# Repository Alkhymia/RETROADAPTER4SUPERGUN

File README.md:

# RETROADAPTER4SUPERGUN

Uses the concept of Paul Quereshi's RetroAdapter, but with CommonGround-Output instead of USB.
Lets you connect a wide range of controllers to a supergun or JAMMA incl SNES, MD, SAT, PSX, N64 etc.

## Work in progress

Right now, only the pcb is provided. The Code for the RetroAdapterMod needs to be rewritten because the pins changed!
If you would like to help finish this project, any help is appreciated.

## PCB Specification

You can order the printed circuit board e.g. from itead.cc using the GERBER files that I provided.

```
50 x 50 mm
1.2 to 1.6 (recommended) mm Thickness
HASL
```

### Installing

* solder all components to the pcb
* Atmega µController needs to be flashed via ISP-PORT.
* connect your favourite joypad to either the DB9 or DB15 connector as shown in the original connection diagram. Bare in mind that the pins may have changed! A detailed new connection diagram will follow in the future.
* connect the output to your JAMMA or SUPERGUN setup.
* Play your arcade games with your favourite controller, such as the Sega Saturn or SNES joypad.

## Links

* Original source for "USB Retropad Adapter" from Bruno Freitas acquired via http://www.brunofreitas.com/node/41 (included for reference in folder original_Files)

* Original source for "Retro Adapter v2.1a" from Paul Qureshi acquired via http://denki.world3.net/retro_v2.html (incuded for reference in folder original_Files)

* https://github.com/rsn8887/RetroAdapterMod

## Built With

* [EAGLE](https://www.autodesk.de/products/eagle/overview)

## Contributing

Please read [CONTRIBUTING.md] for details on our code of conduct, and the process for submitting pull requests to us.

## Authors

* **Alex Schütz** - *Concept & PCB Design*
* **rsn8887** - *RetroAdapterMod*
* **Paul Qureshi** - *RetroAdapter*

See also the list of [contributors](https://github.com/your/project/contributors) who participated in this project.

## License

This project is licensed under the MIT License - see the [LICENSE.md](LICENSE.md) file for details

## Acknowledgments

* This is a work in progress.
* Don't mess with electronics if you don't know what you're doing!

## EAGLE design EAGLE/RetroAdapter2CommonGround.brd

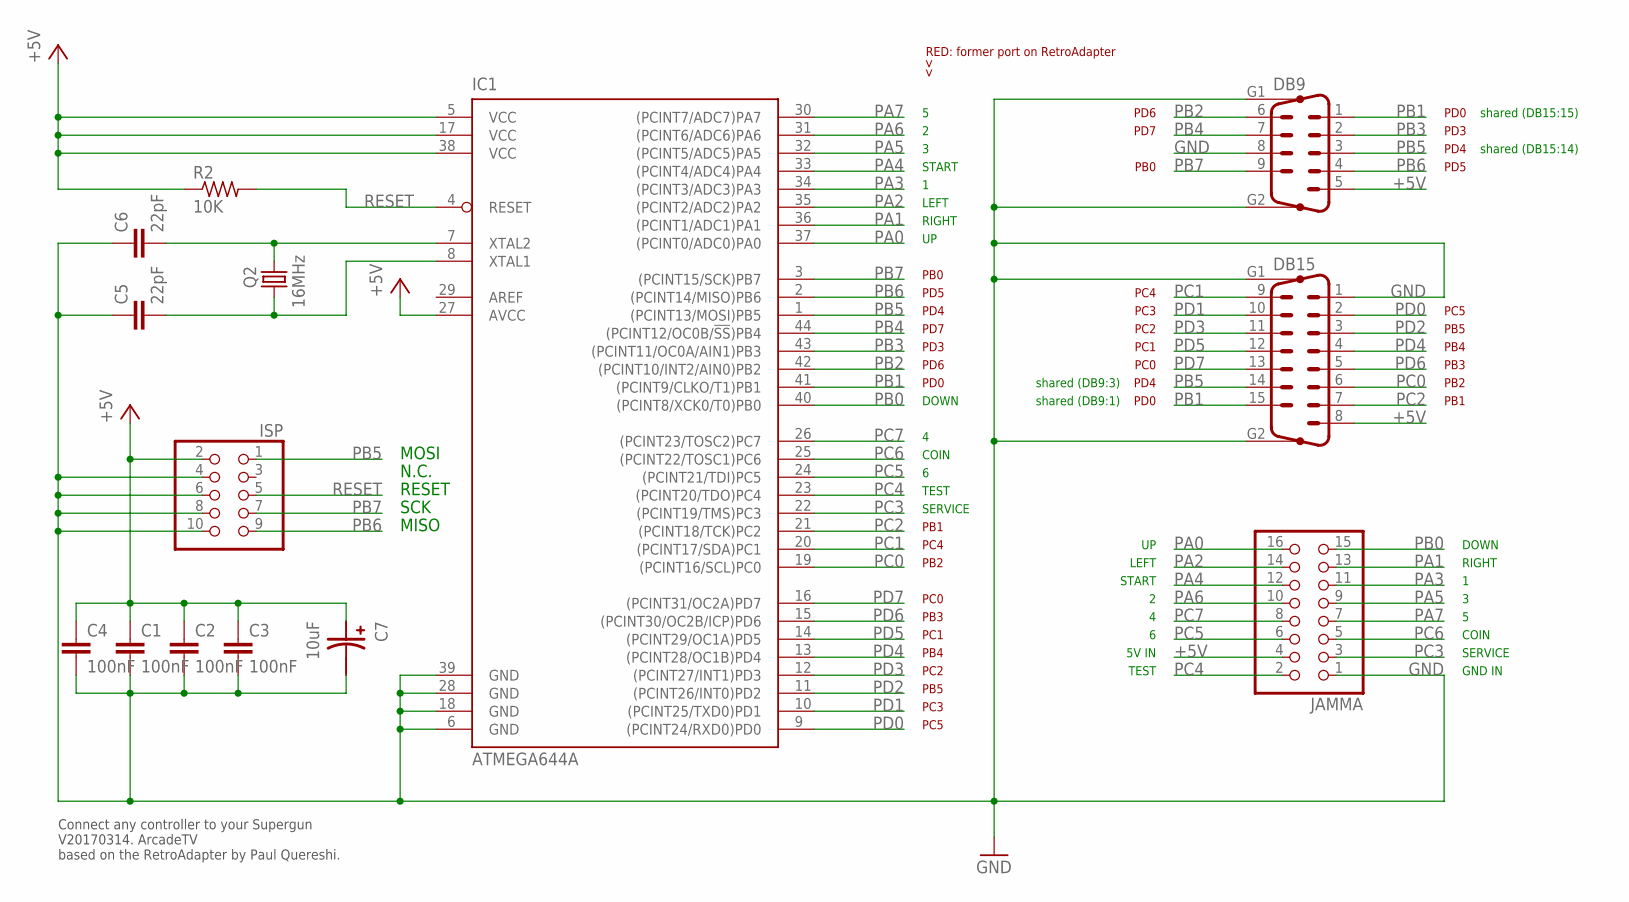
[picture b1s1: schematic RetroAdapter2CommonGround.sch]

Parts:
C1, C2, C3, C4: 100nF; Z0805
C5, C6: 22pF; Z0805
C7: 10uF; EEEFPJ101UAR_PANASONIC_VFP-SERIES
DB9: M09HP
DB15: M15HP
IC1: ATMEGA644A; TQFP44
ISP: PINHD-2X5; 2X05
JAMMA: PINHD-2X8; 2X08
Q2: 16MHz; HC49/S
R2: 10K; R0603

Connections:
+5V: C1.1, C2.1, C3.1, C4.1, C7.PLUS (+), DB9.5, DB15.8, IC1.5 (VCC), IC1.17 (VCC), IC1.27 (AVCC), IC1.38 (VCC), ISP.2, JAMMA.4, R2.1
GND: C1.2, C2.2, C3.2, C4.2, C5.1, C6.1, C7.MINUS (-), DB9.8, DB9.G1, DB9.G2, DB15.1, DB15.G1, DB15.G2, IC1.6 (GND), IC1.18 (GND), IC1.28 (GND), IC1.39 (GND), ISP.4, ISP.6, ISP.8, ISP.10, JAMMA.1
unnamed: C5.2, IC1.8 (XTAL1), Q2.1
unnamed: C6.2, IC1.7 (XTAL2), Q2.2
PA0: IC1.37 ((PCINT0/ADC0)PA0), JAMMA.16
PA1: IC1.36 ((PCINT1/ADC1)PA1), JAMMA.13
PA2: IC1.35 ((PCINT2/ADC2)PA2), JAMMA.14
PA3: IC1.34 ((PCINT3/ADC3)PA3), JAMMA.11
PA4: IC1.33 ((PCINT4/ADC4)PA4), JAMMA.12
PA5: IC1.32 ((PCINT5/ADC5)PA5), JAMMA.9
PA6: IC1.31 ((PCINT6/ADC6)PA6), JAMMA.10
PA7: IC1.30 ((PCINT7/ADC7)PA7), JAMMA.7
PB0: IC1.40 ((PCINT8/XCK0/T0)PB0), JAMMA.15
PB1: DB9.1, DB15.15, IC1.41 ((PCINT9/CLKO/T1)PB1)
PB2: DB9.6, IC1.42 ((PCINT10/INT2/AIN0)PB2)
PB3: DB9.2, IC1.43 ((PCINT11/OC0A/AIN1)PB3)
PB4: DB9.7, IC1.44 ((PCINT12/OC0B/!SS!)PB4)
PB5: DB9.3, DB15.14, IC1.1 ((PCINT13/MOSI)PB5), ISP.1
PB6: DB9.4, IC1.2 ((PCINT14/MISO)PB6), ISP.9
PB7: DB9.9, IC1.3 ((PCINT15/SCK)PB7), ISP.7
PC0: DB15.6, IC1.19 ((PCINT16/SCL)PC0)
PC1: DB15.9, IC1.20 ((PCINT17/SDA)PC1)
PC2: DB15.7, IC1.21 ((PCINT18/TCK)PC2)
PC3: IC1.22 ((PCINT19/TMS)PC3), JAMMA.3
PC4: IC1.23 ((PCINT20/TDO)PC4), JAMMA.2
PC5: IC1.24 ((PCINT21/TDI)PC5), JAMMA.6
PC6: IC1.25 ((PCINT22/TOSC1)PC6), JAMMA.5
PC7: IC1.26 ((PCINT23/TOSC2)PC7), JAMMA.8
PD0: DB15.2, IC1.9 ((PCINT24/RXD0)PD0)
PD1: DB15.10, IC1.10 ((PCINT25/TXD0)PD1)
PD2: DB15.3, IC1.11 ((PCINT26/INT0)PD2)
PD3: DB15.11, IC1.12 ((PCINT27/INT1)PD3)
PD4: DB15.4, IC1.13 ((PCINT28/OC1B)PD4)
PD5: DB15.12, IC1.14 ((PCINT29/OC1A)PD5)
PD6: DB15.5, IC1.15 ((PCINT30/OC2B/ICP)PD6)
PD7: DB15.13, IC1.16 ((PCINT31/OC2A)PD7)
RESET: IC1.4 (RESET), ISP.5, R2.2

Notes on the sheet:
MOSI
MISO
SCK
RESET
N.C.
Connect any controller to your Supergun V20170314. ArcadeTV based on the RetroAdapter by Paul Quereshi.
PD0
PD3
PD4
PD5
PD6
PD7
PB0
RED: former port on RetroAdapter
PC5
PB4
PB3
PB2
PB1
PC3
PC4
PB5
PC2
PC1
PC0
shared (DB9:3)
shared (DB9:1)
shared (DB15:15)
shared (DB15:14)
LEFT
START
5V IN
TEST
DOWN
RIGHT
COIN
SERVICE
GND IN

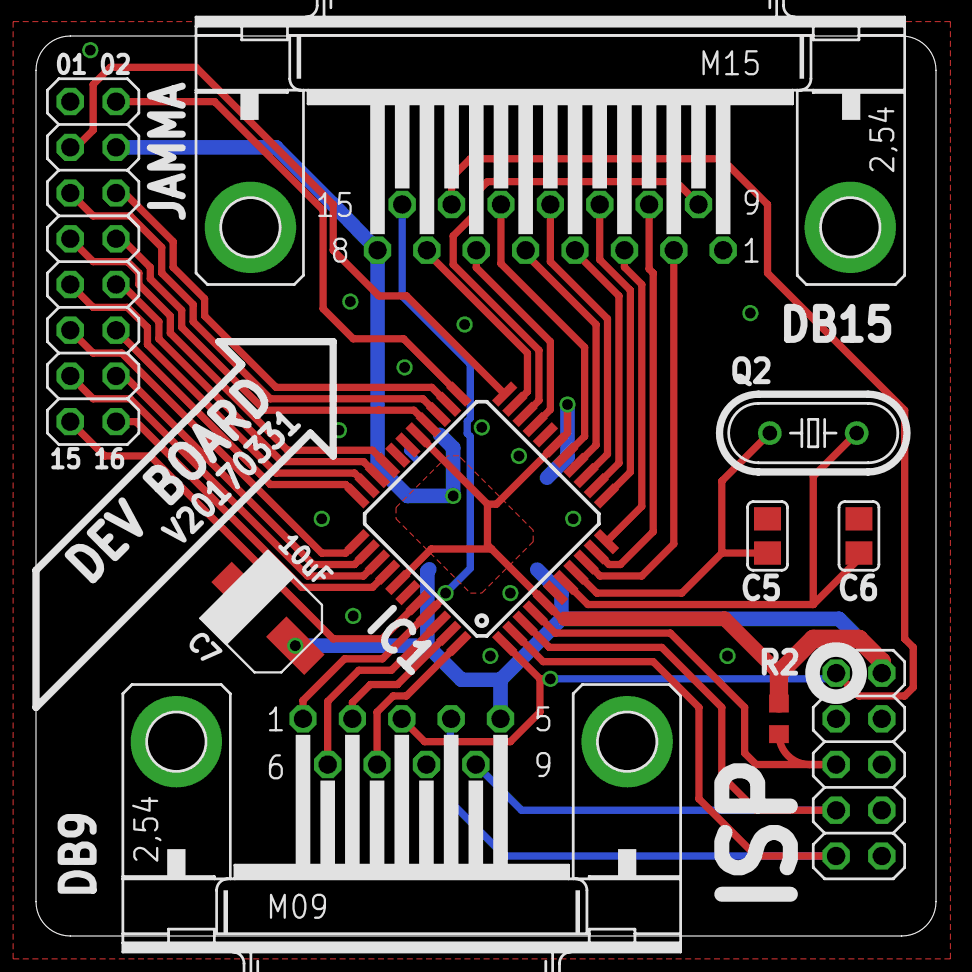
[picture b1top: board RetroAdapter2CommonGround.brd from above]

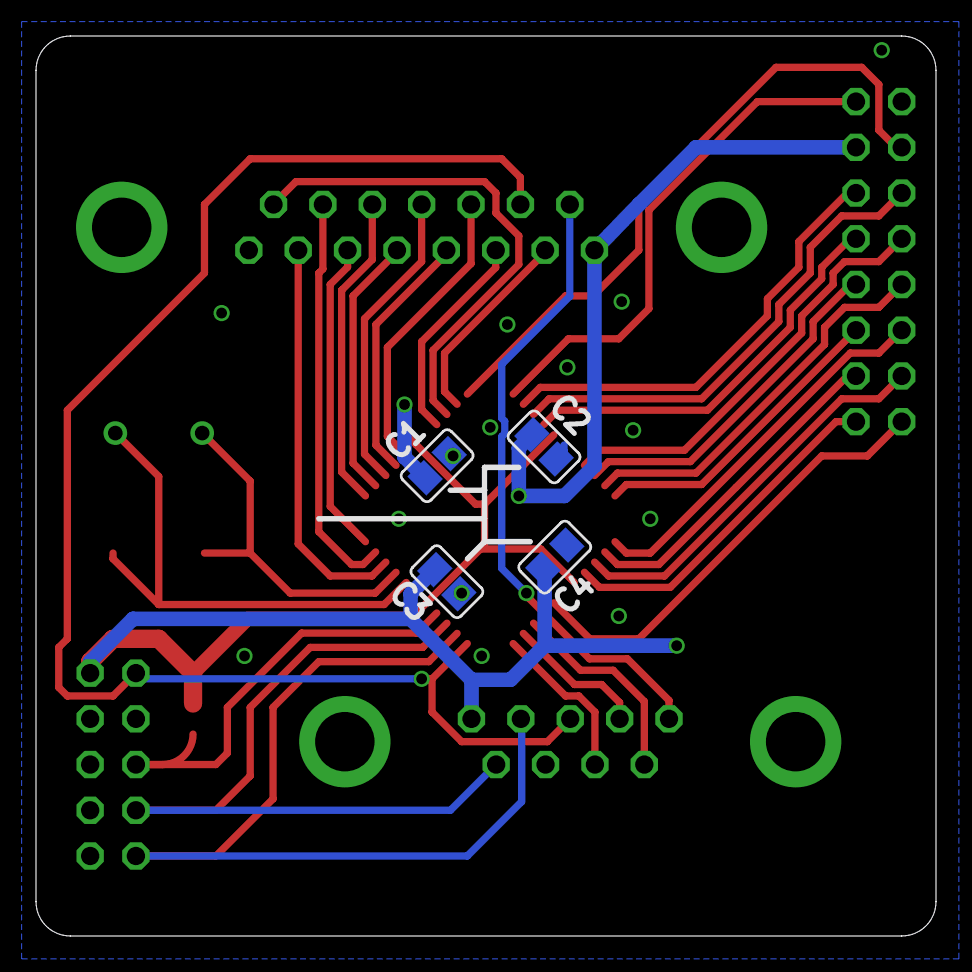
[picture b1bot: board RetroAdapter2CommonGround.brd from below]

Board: 2 copper layers, 50.0 x 50.0 mm, 14 parts (4 on the bottom side), 37 nets.

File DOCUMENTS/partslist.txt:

Partlist

Exported from RetroAdapter2CommonGround.sch at 23.03.17 09:13

EAGLE Version 8.1.0 Copyright (c) 1988-2017 Autodesk, Inc.

Assembly variant: 

Part     Value          Device                            Package                           Library  Sheet

C1       100nF          C0805                             Z0805                             arcadetv 1
C2       100nF          C0805                             Z0805                             arcadetv 1
C3       100nF          C0805                             Z0805                             arcadetv 1
C4       100nF          C0805                             Z0805                             arcadetv 1
C5       22pF           C0805                             Z0805                             arcadetv 1
C6       22pF           C0805                             Z0805                             arcadetv 1
C7       10uF           EEEFPJ101UAR_PANASONIC_VFP-SERIES EEEFPJ101UAR_PANASONIC_VFP-SERIES arcadetv 1
DB9                     M09HP                             M09HP                             con-subd 1
DB15                    M15HP                             M15HP                             con-subd 1
IC1      ATMEGA644A     ATMEGA644A                        TQFP44                            arcadetv 1
ISP                     PINHD-2X5                         2X05                              pinhead  1
JAMMA                   PINHD-2X8                         2X08                              pinhead  1
Q2       15MHz          CRYSTALHC49S                      HC49/S                            crystal  1
R2       10K            R-US_R0603                        R0603                             rcl      1

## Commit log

2017-07-19 Create LICENSE
